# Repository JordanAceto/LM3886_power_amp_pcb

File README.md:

# Evaluation board for LM3886 based chip amps.

## Status of the project:

Revision | schematic | pcb layout | built and tested | documentation
---------|-----------|------------|------------------|---------------
1        | &#9745;   | &#9745;    | &#9745;          | &#9745;

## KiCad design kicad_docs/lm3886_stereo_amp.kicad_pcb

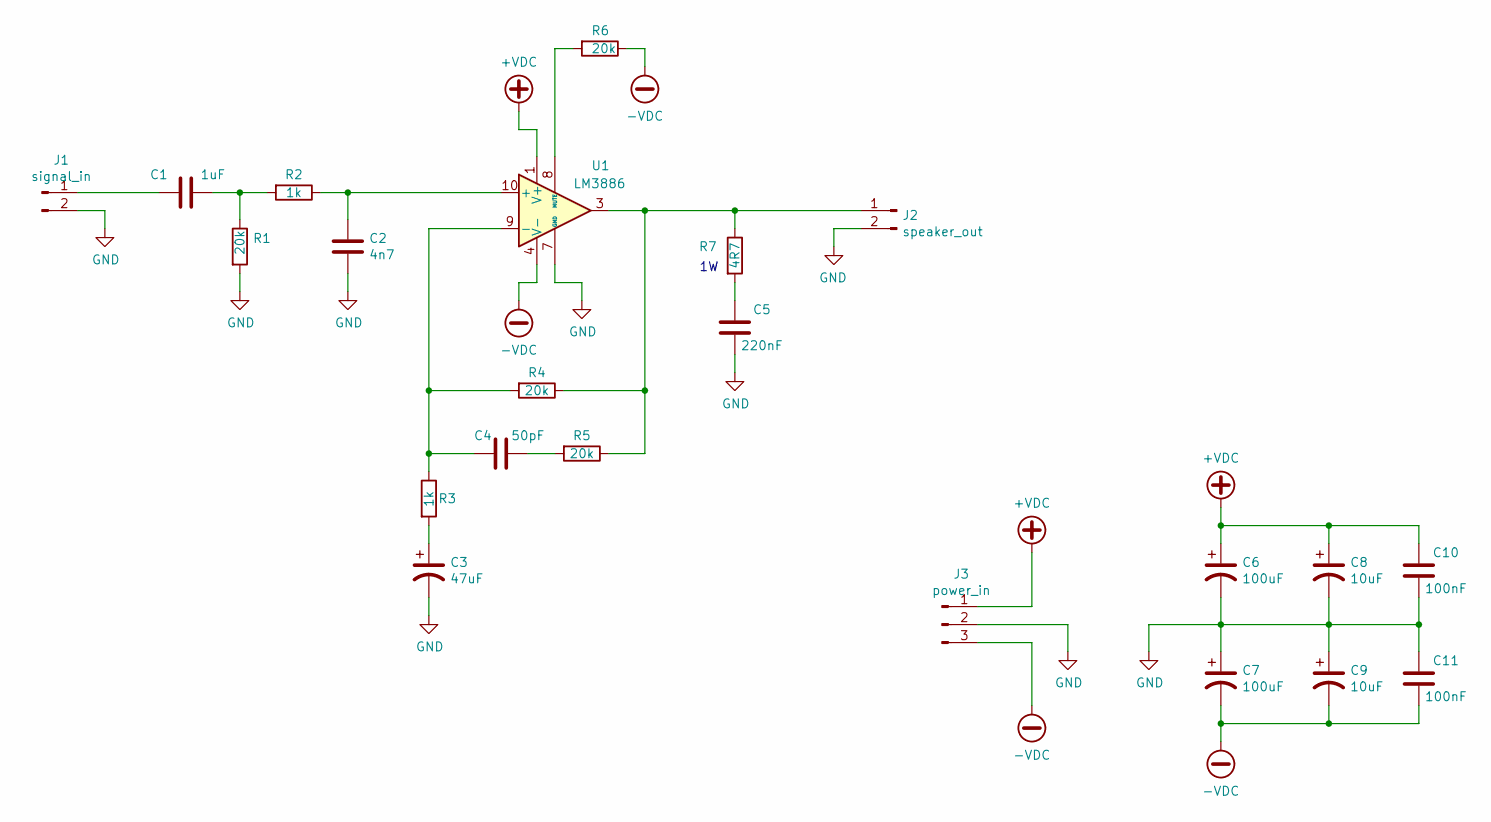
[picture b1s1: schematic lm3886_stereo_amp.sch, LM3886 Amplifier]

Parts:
C1: 1uF; C_Rect_L7.0mm_W3.5mm_P5.00mm
C2: 4n7; C_Rect_L7.0mm_W2.5mm_P5.00mm
C3: 47uF; CP_Radial_D10.0mm_P5.00mm
C4: 50pF; C_0805_2012Metric_Pad1.15x1.40mm_HandSolder
C5: 220nF; C_Rect_L7.0mm_W3.5mm_P5.00mm
C6, C7: 100uF; CP_Radial_D10.0mm_P5.00mm
C8, C9: 10uF; CP_Radial_D5.0mm_P2.50mm
C10, C11: 100nF; C_0805_2012Metric_Pad1.15x1.40mm_HandSolder
J1: signal_in; SolderWirePad_1x02_P3.81mm_Drill1.2mm
J2: speaker_out; SolderWirePad_1x02_P5.08mm_Drill1.5mm
J3: power_in; SolderWirePad_1x03_P4.445mm_Drill1.5mm
R1, R4, R5, R6: 20k; R_0805_2012Metric_Pad1.15x1.40mm_HandSolder
R2, R3: 1k; R_0805_2012Metric_Pad1.15x1.40mm_HandSolder
R7: 4R7; R_Axial_DIN0411_L9.9mm_D3.6mm_P15.24mm_Horizontal
U1: LM3886; TO-220-11_P3.4x5.08mm_StaggerOdd_Lead4.85mm_Vertical

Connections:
+VDC: C6.1, C8.1, C10.1, J3.1, U1.1 (V+), U1.5 (V+)
-VDC: C7.2, C9.2, C11.2, J3.3, R6.1, U1.4 (V-)
GND: C2.2, C3.2, C5.2, C6.2, C7.1, C8.2, C9.1, C10.2, C11.1, J1.2, J2.2, J3.2, R1.2, U1.7 (GND)
unnamed: C1.1, R1.1, R2.2
unnamed: C1.2, J1.1
unnamed: C2.1, R2.1, U1.10 (+)
unnamed: C3.1, R3.2
unnamed: C4.1, R5.2
unnamed: C4.2, R3.1, R4.2, U1.9 (-)
unnamed: C5.1, R7.2
unnamed: J2.1, R4.1, R5.1, R7.1, U1.3
unnamed: R6.2, U1.8 (MUTE)

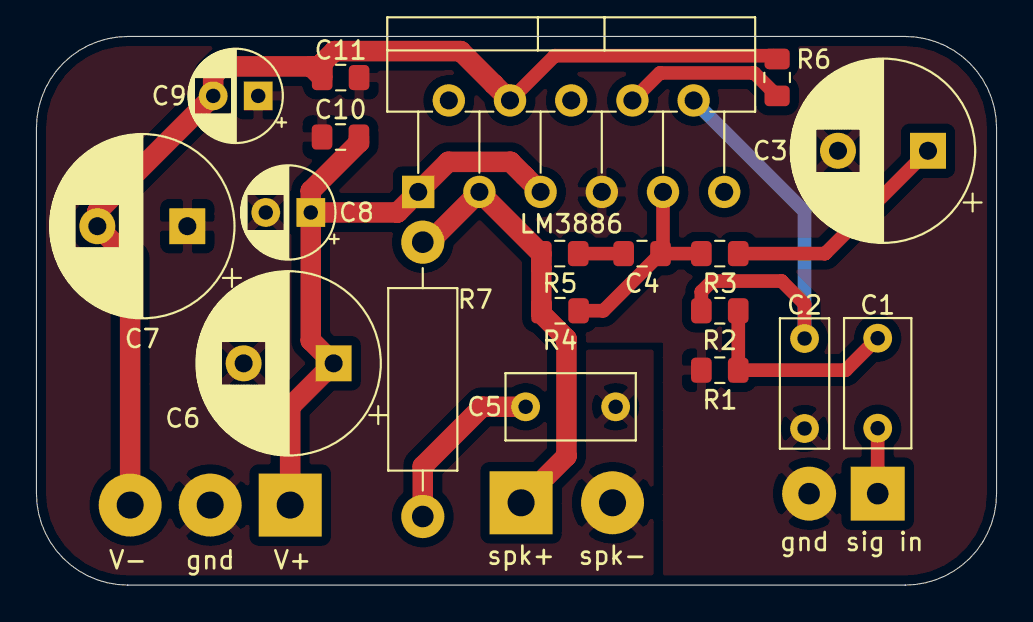
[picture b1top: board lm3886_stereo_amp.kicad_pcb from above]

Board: 2 copper layers, 53.3 x 30.5 mm, 22 parts (0 on the bottom side), 12 nets.

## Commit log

2020-02-23 create directory structure, add pics and readme
2020-02-23 add schematic pdf
2020-02-23 Create LICENSE
2020-08-21 add gitignore for kicad files
2020-08-21 redesign pcb for easier to source components

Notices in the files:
kicad_docs/lm3886_stereo_amp.kicad_pcb:
License: CC by 4.0
kicad_docs/lm3886_stereo_amp.sch:
creativecommons.org/licenses/by/4.0
